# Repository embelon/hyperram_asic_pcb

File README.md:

# hyperram_asic_pcb
Test PCB for CARAVEL ASIC manufactured by efables.com in Open Source Shuttles to check HyperRAM memory controller IP connected to RISC-V through Wishbone bus.

HyperRAM controller was submitted in MPW-2 as part of multi project: 
https://platform.efabless.com/projects/66
and in MPW-3 on its own (with additional 1kB of OpenRAM):
https://platform.efabless.com/projects/501

HyperRAM controller IP was created to work with Cypress S27KL0641:
https://github.com/embelon/wb_hyperram

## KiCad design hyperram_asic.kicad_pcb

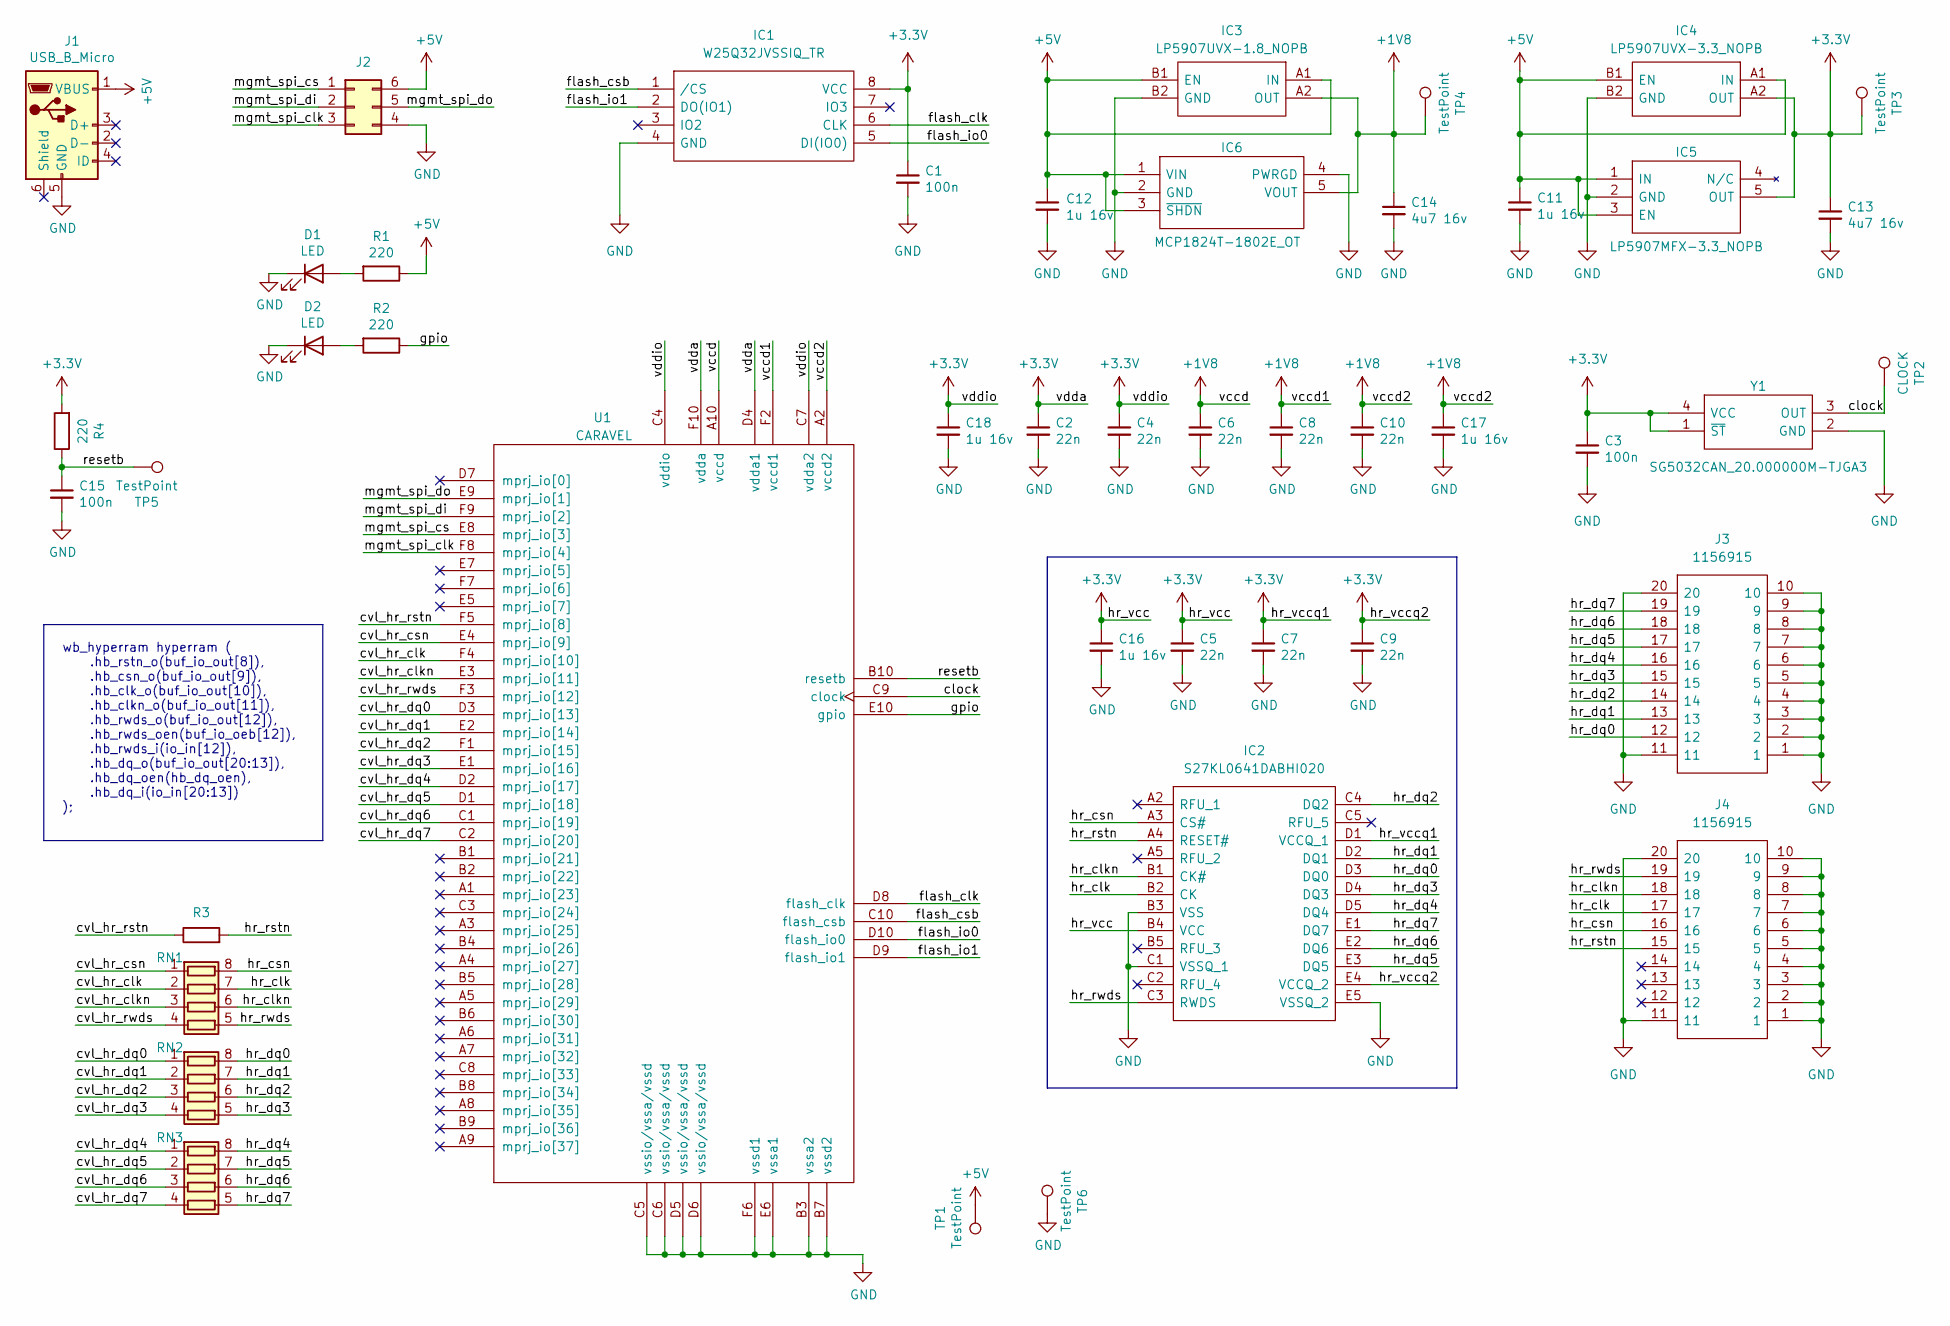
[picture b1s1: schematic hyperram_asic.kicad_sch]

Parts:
C1, C3, C15: 100n; C_0402_1005Metric_Pad0.74x0.62mm_HandSolder; Part CGA3E2X7R1H223K080AA
C2, C4, C5, C6, C7, C8, C9, C10: 22n; C_0402_1005Metric_Pad0.74x0.62mm_HandSolder; Part CGA3E2X7R1H223K080AA
C11, C12, C16, C17, C18: 1u 16v; C_0805_2012Metric_Pad1.18x1.45mm_HandSolder; Part CL10A105KO8NNNC
C13, C14: 4u7 16v; C_0805_2012Metric_Pad1.18x1.45mm_HandSolder; Part CC0603KRX5R7BB475
D1, D2: LED; LED_0805_2012Metric_Pad1.15x1.40mm_HandSolder; Part LS Q976-NR-1
IC1: W25Q32JVSSIQ_TR; SOIC127P790X216-8N; Mouser Part Number 454-W25Q32JVSSIQTR
IC2: S27KL0641DABHI020; BGA24C100P5X5_600X800X100; Manufacturer_Part_Number S27KL0641DABHI020; Mouser Part Number 727-S27KL0641DABHI02
IC3: LP5907UVX-1.8_NOPB; BGA4C35P2X2_64X64X44; Mouser Part Number 926-LP5907UVX1.8NOPB
IC4: LP5907UVX-3.3_NOPB; BGA4C35P2X2_64X64X33; Mouser Part Number 926-LP5907UVX3.3NOPB
IC5: LP5907MFX-3.3_NOPB; SOT95P280X145-5N; Mouser Part Number 595-LP5907MFX-3.3NPB
IC6: MCP1824T-1802E_OT; SOT95P270X145-5N; Mouser Part Number 579-MCP1824T-1802EOT
J1: USB_B_Micro; UJ2MIBHGSMTTR; Part 105017-0001
J2: Conn_02x03_Counter_Clockwise; PinHeader_2x03_P2.54mm_Vertical
J3, J4: 1156915; Mouser Part Number 651-1156915
R1, R2, R4: 220; R_0603_1608Metric; Part ‎RC0603JR-07100RL‎
R3: R; R_0603_1608Metric
RN1, RN2, RN3: CAY16-22R0F4LF; CAY16000J4LF
TP1, TP3, TP4, TP5, TP6: TestPoint; TestPoint_Pad_D1.0mm
TP2: CLOCK; TestPoint_Pad_D1.0mm
U1: CARAVEL; WLCSP-60_P0.5mm
Y1: SG5032CAN_20.000000M-TJGA3; SG5032CAN20000000MTJGA3; Mouser Part Number 732-5032CAN20.0TJGA3

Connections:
+1V8: C6.1, C8.1, C10.1, C14.1, C17.1, IC3.A2 (OUT), IC6.5 (VOUT), TP4.1, U1.A2 (vccd2), U1.A10 (vccd), U1.F2 (vccd1)
+3V3: C1.1, C2.1, C3.1, C4.1, C5.1, C7.1, C9.1, C13.1, C16.1, C18.1, IC1.8 (VCC), IC2.B4 (VCC), IC2.D1 (VCCQ_1), IC2.E4 (VCCQ_2), IC4.A2 (OUT), IC5.5 (OUT), R4.2, TP3.1, U1.C4 (vddio), U1.C7 (vdda2), U1.D4 (vdda1), U1.F10 (vdda), Y1.1 (~ST), Y1.4 (VCC)
+5V: C11.1, C12.1, IC3.A1 (IN), IC3.B1 (EN), IC4.A1 (IN), IC4.B1 (EN), IC5.1 (IN), IC5.3 (EN), IC6.1 (VIN), IC6.3 (~SHDN), J1.1 (VBUS), J2.6, R1.1, TP1.1
/clock: TP2.1, U1.C9 (clock), Y1.3 (OUT)
/cvl_hr_clk: RN1.2 (R2.1), U1.F4 (mprj_io[10])
/cvl_hr_clkn: RN1.3 (R3.1), U1.E3 (mprj_io[11])
/cvl_hr_csn: RN1.1 (R1.1), U1.E4 (mprj_io[9])
/cvl_hr_dq0: RN2.1 (R1.1), U1.D3 (mprj_io[13])
/cvl_hr_dq1: RN2.2 (R2.1), U1.E2 (mprj_io[14])
/cvl_hr_dq2: RN2.3 (R3.1), U1.F1 (mprj_io[15])
/cvl_hr_dq3: RN2.4 (R4.1), U1.E1 (mprj_io[16])
/cvl_hr_dq4: RN3.1 (R1.1), U1.D2 (mprj_io[17])
/cvl_hr_dq5: RN3.2 (R2.1), U1.D1 (mprj_io[18])
/cvl_hr_dq6: RN3.3 (R3.1), U1.C1 (mprj_io[19])
/cvl_hr_dq7: RN3.4 (R4.1), U1.C2 (mprj_io[20])
/cvl_hr_rstn: R3.1, U1.F5 (mprj_io[8])
/cvl_hr_rwds: RN1.4 (R4.1), U1.F3 (mprj_io[12])
/flash_clk: IC1.6 (CLK), U1.D8 (flash_clk)
/flash_csb: IC1.1 (/CS), U1.C10 (flash_csb)
/flash_io0: IC1.5 (DI(IO0)), U1.D10 (flash_io0)
/flash_io1: IC1.2 (DO(IO1)), U1.D9 (flash_io1)
/gpio: R2.1, U1.E10 (gpio)
/hr_clk: IC2.B2 (CK), J4.17, RN1.7 (R2.2)
/hr_clkn: IC2.B1 (CK#), J4.18, RN1.6 (R3.2)
/hr_csn: IC2.A3 (CS#), J4.16, RN1.8 (R1.2)
/hr_dq0: IC2.D3 (DQ0), J3.12, RN2.8 (R1.2)
/hr_dq1: IC2.D2 (DQ1), J3.13, RN2.7 (R2.2)
/hr_dq2: IC2.C4 (DQ2), J3.14, RN2.6 (R3.2)
/hr_dq3: IC2.D4 (DQ3), J3.15, RN2.5 (R4.2)
/hr_dq4: IC2.D5 (DQ4), J3.16, RN3.8 (R1.2)
/hr_dq5: IC2.E3 (DQ5), J3.17, RN3.7 (R2.2)
/hr_dq6: IC2.E2 (DQ6), J3.18, RN3.6 (R3.2)
/hr_dq7: IC2.E1 (DQ7), J3.19, RN3.5 (R4.2)
/hr_rstn: IC2.A4 (RESET#), J4.15, R3.2
/hr_rwds: IC2.C3 (RWDS), J4.19, RN1.5 (R4.2)
/mgmt_spi_clk: J2.3, U1.F8 (mprj_io[4])
/mgmt_spi_cs: J2.1, U1.E8 (mprj_io[3])
/mgmt_spi_di: J2.2, U1.F9 (mprj_io[2])
/mgmt_spi_do: J2.5, U1.E9 (mprj_io[1])
/resetb: C15.1, R4.1, TP5.1, U1.B10 (resetb)
GND: C1.2, C2.2, C3.2, C4.2, C5.2, C6.2, C7.2, C8.2, C9.2, C10.2, C11.2, C12.2, C13.2, C14.2, C15.2, C16.2, C17.2, C18.2, D1.1 (K), D2.1 (K), IC1.4 (GND), IC2.B3 (VSS), IC2.C1 (VSSQ_1), IC2.E5 (VSSQ_2), IC3.B2 (GND), IC4.B2 (GND), IC5.2 (GND), IC6.2 (GND), IC6.4 (PWRGD), J1.5 (GND), J2.4, J3.1, J3.2, J3.3, J3.4, J3.5, J3.6, J3.7, J3.8, J3.9, J3.10, J3.11, J3.20, J4.1, J4.2, J4.3, J4.4, J4.5, J4.6, J4.7, J4.8, J4.9, J4.10, J4.11, J4.20, TP6.1, U1.B3 (vssa2), U1.B7 (vssd2), U1.C5 (vssio/vssa/vssd), U1.C6 (vssio/vssa/vssd), U1.D5 (vssio/vssa/vssd), U1.D6 (vssio/vssa/vssd), U1.E6 (vssa1), U1.F6 (vssd1), Y1.2 (GND)
unnamed: D1.2 (A), R1.2
unnamed: D2.2 (A), R2.2

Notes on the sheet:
wb_hyperram hyperram ( .hb_rstn_o(buf_io_out[8]), .hb_csn_o(buf_io_out[9]), .hb_clk_o(buf_io_out[10]), .hb_clkn_o(buf_io_out[11]), .hb_rwds_o(buf_io_out[12]), .hb_rwds_oen(buf_io_oeb[12]), .hb_rwds_i(io_in[12]), .hb_dq_o(buf_io_out[20:13]), .hb_dq_oen(hb_dq_oen), .hb_dq_i(io_in[20:13]) );

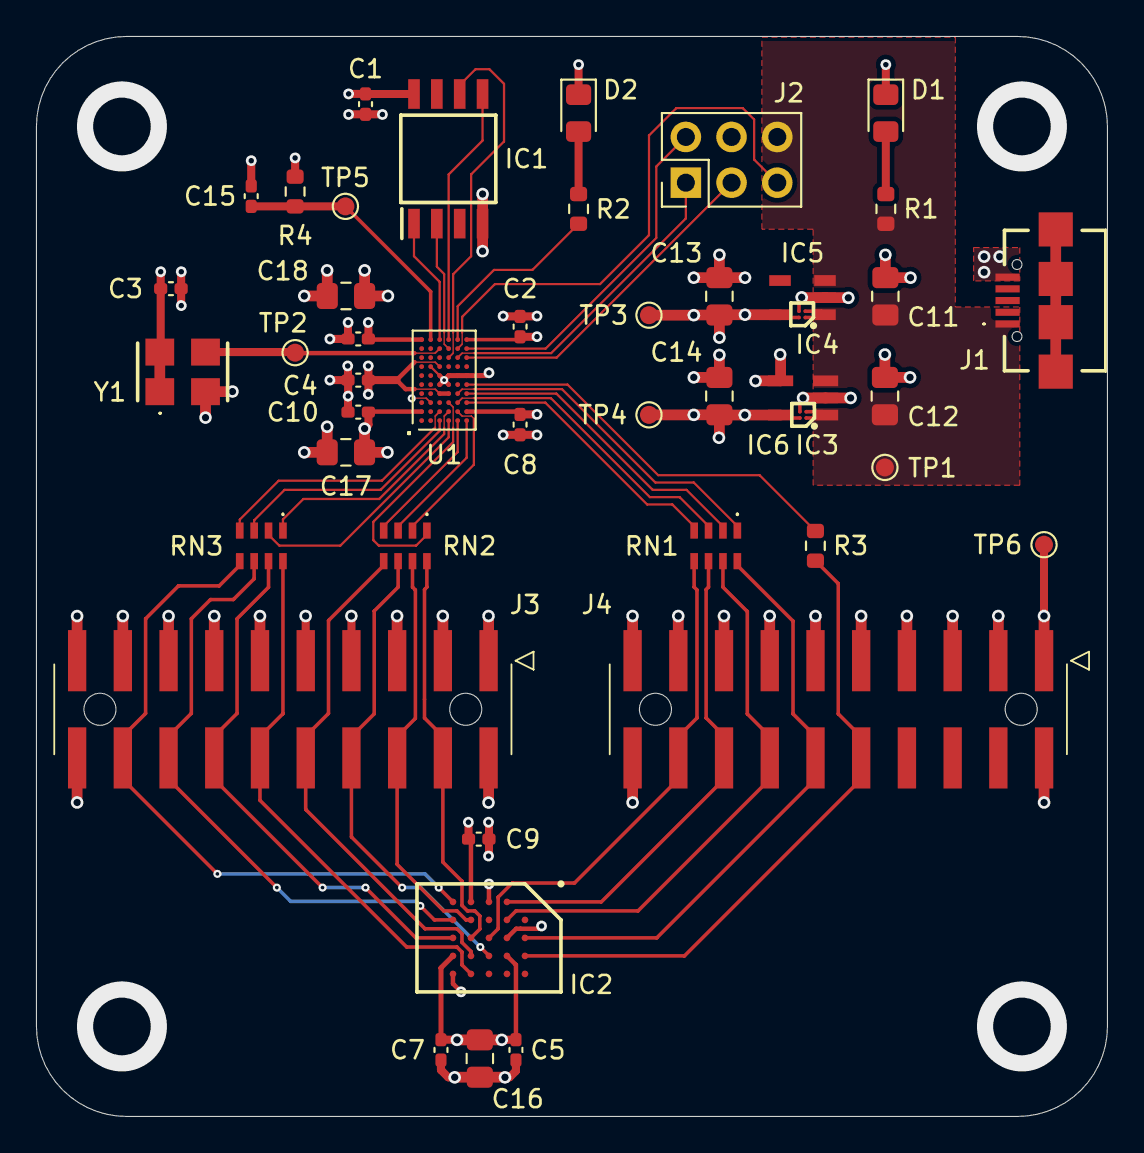
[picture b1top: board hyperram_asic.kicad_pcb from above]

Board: 4 copper layers, 59.5 x 60.0 mm, 45 parts (0 on the bottom side), 43 nets.

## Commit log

2022-09-03 PCB ready for manufacturing... at least it seems so.
